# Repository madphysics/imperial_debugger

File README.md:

View this project on [CADLAB.io](https://cadlab.io/project/1894). 

# Imperial Debugger V1.1 #

USB Based multi serial port adaptor

## Overview ##

Based on an FTDI FT4232HL USB to serial chip, with 4 ports. 

The plan is to bring all points to bring them out to a standard 2x6 header

Then can use external daughter boards to do things like:

 * 1x RS232 with hardware flow control
 * 1x RS422/485 with configuration to switch between the two, wither in software or hardware.
 * 1x RS232/422 selectable
 * 1x Logic level, with external level shifter (selectable to internal 3v3)
  
## Power Supply ##

Simple switching mode from 5V USB to 3v3 on the board.
 
## Potential XCVR chips

### RS232
  * TI MAX3222E -- Looks good. Has protection in it. 250k min speeds.
    * MAX3222EEWN is WideSOIC
	  * Also available in SSOP 20 pin, which is harder to solder.
    * 4 signals, so TX/RX and CTS/RTS
	* 3222 has a shutdown pin, Active Low.

### RS422/485

  * MAX3491E
  * MAX22503
  * MAX3070-3073-3076 (3076 is fastest, all pin compatible)
  * SP330 (can do 232 as well, so could use just 3 of these?)
  
### Logic level
 
  * Ideally we want to go from 3v3 ->5V but also 3v3 > lower (2.5, 1.8)
  * LSF0204, can do 3v3 down to Ref\_A. Ref\_B Is always the higher
  * To generate 3v3 > 5V need a different route, where the signals are reversed
    Such that the input is on the Ref_B side, so could use 2 sets and jumper it.
	* Could use 3 pin jumpers, to direct the signal to one of two, or maybe use
	bus selector chip to auto do it.
  * Most ttl/cmos all work the same.

  * LSF0102 - nexperia
  * NCA9306DC - nexperia

## Potential PSU design

 * LM2594M
   * In stock, cheap.
   * ~500mA Output
   * -- **Initial choice**
 * MIC4680
   * In stock.
   * ~1A output
 * TPS5403
   * Hard to get hold of, but in stock.
 * LT1506
   * Expensive. Hard to get.
   
## Notes

 * Use externnal eeprom (SPI based) this will allow the usage of the nRI as a TXEN line for RS422/485 usage
   * 93LC56B is recommended. 16bit wide 2Kb eeprom.

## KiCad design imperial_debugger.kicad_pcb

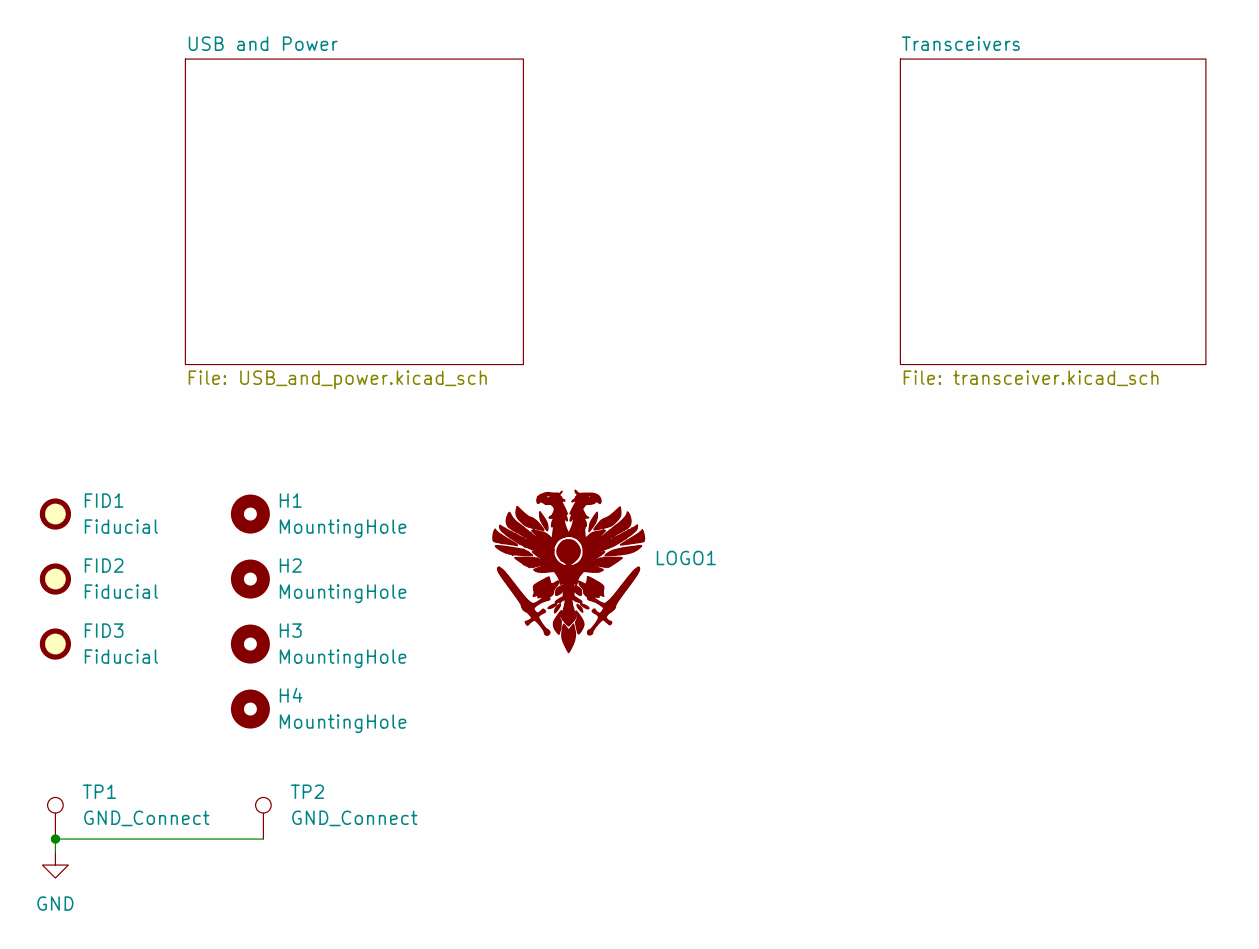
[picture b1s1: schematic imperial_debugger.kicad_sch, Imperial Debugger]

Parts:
FID1, FID2, FID3: Fiducial; Fiducial_1.5mm_Mask3mm
H1, H2, H3, H4: MountingHole; MountingHole_3.2mm_M3
LOGO1: achenar_logo
TP1, TP2: GND_Connect; TestPoint_Keystone_5000-5004_Miniature

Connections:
GND: TP1.1 (1_1), TP2.1 (1_1); also elsewhere on the board

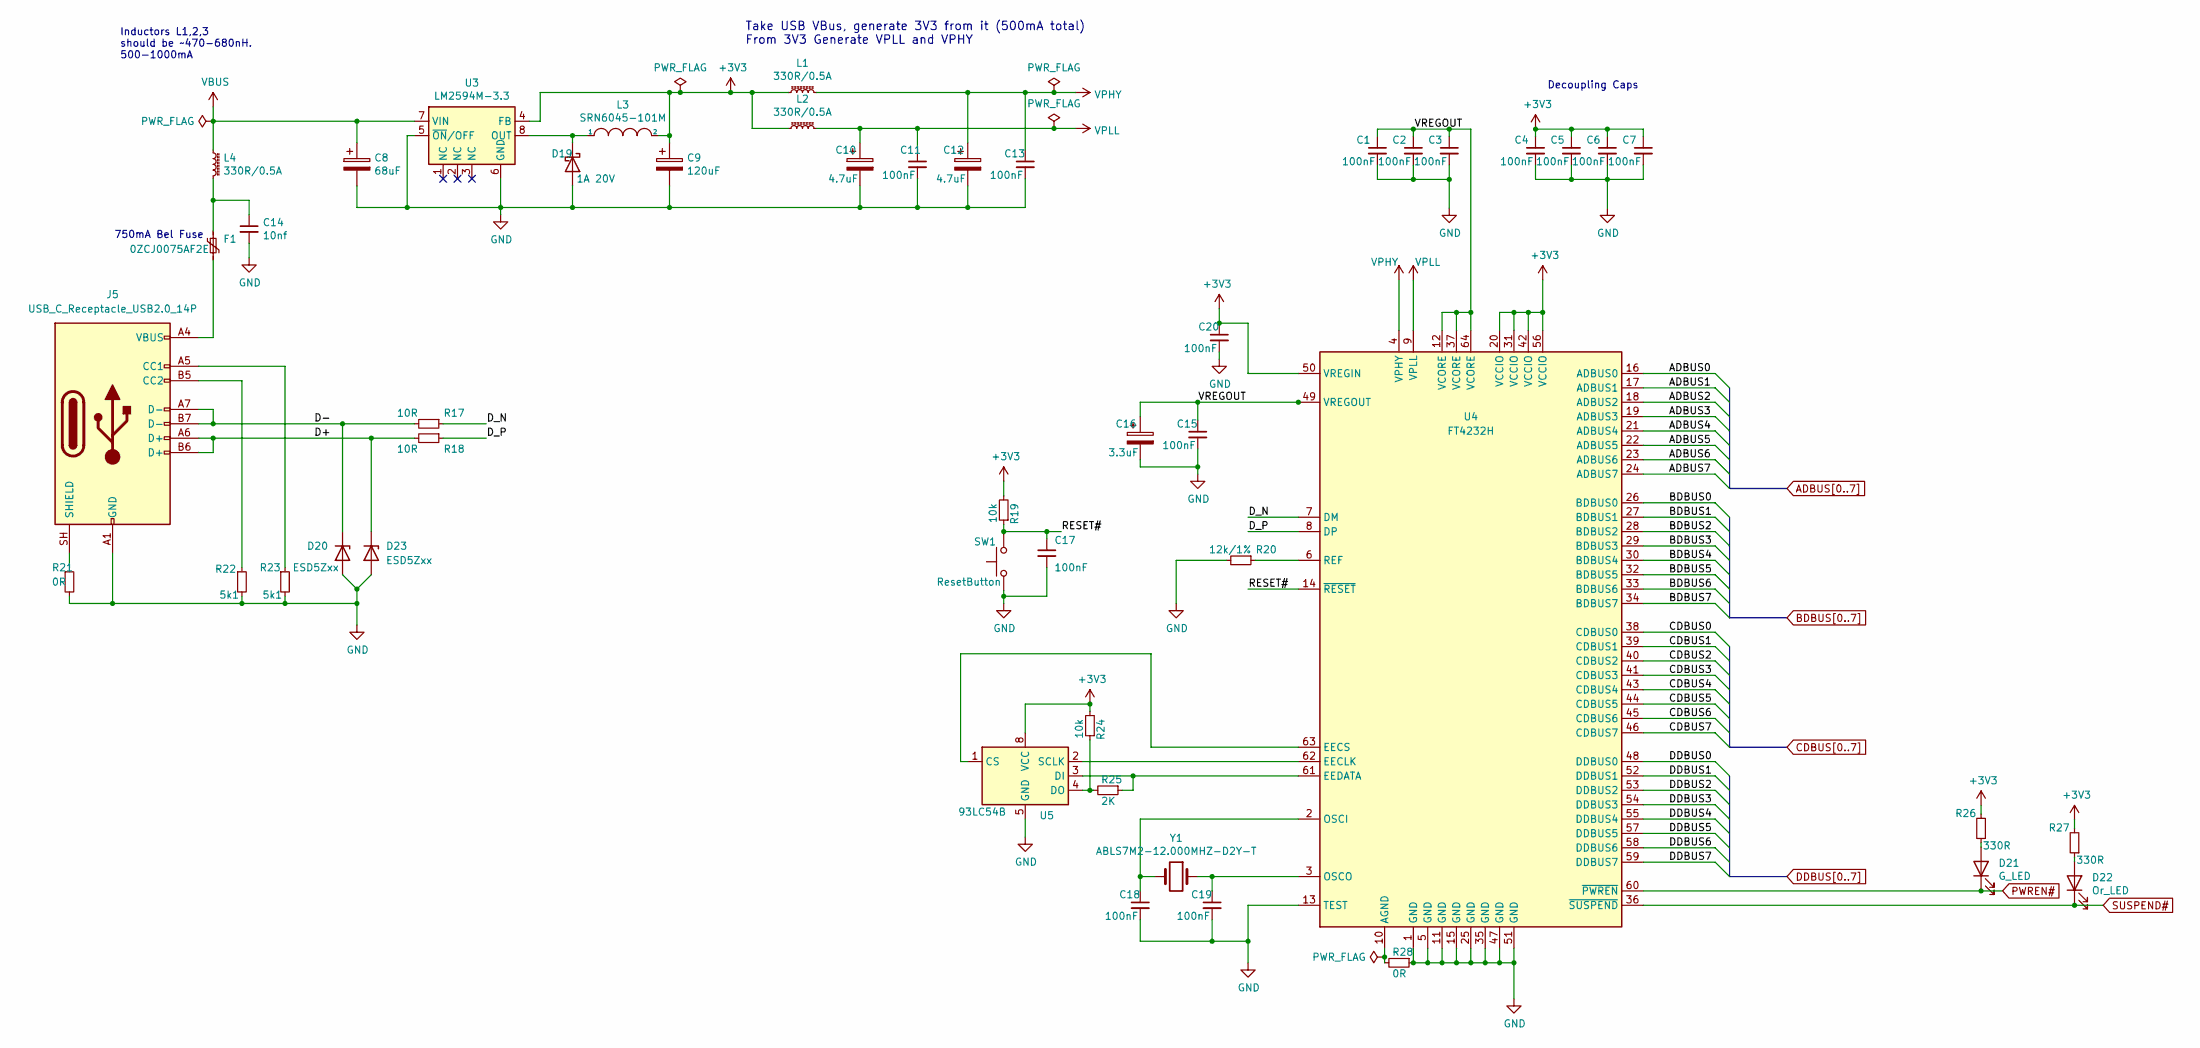
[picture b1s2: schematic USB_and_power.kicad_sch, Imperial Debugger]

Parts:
C1, C2, C3, C4, C5, C6, C7, C11, C13, C15, C17, C18, C19, C20: 100nF; C_0603_1608Metric_Pad1.08x0.95mm_HandSolder
C8: 68uF; CP_EIA-3528-21_Kemet-B_HandSolder
C9: 120uF; CP_Elec_6.3x5.7
C10, C12: 4.7uF; C_0603_1608Metric_Pad1.08x0.95mm_HandSolder
C14: 10nf; C_0603_1608Metric_Pad1.08x0.95mm_HandSolder
C16: 3.3uF; C_0603_1608Metric_Pad1.08x0.95mm_HandSolder
D19: 1A 20V; D_SOD-123
D20, D23: ESD5Zxx; D_SOD-523
D21: G_LED; LED_0603_1608Metric_Pad1.05x0.95mm_HandSolder
D22: Or_LED; LED_0603_1608Metric_Pad1.05x0.95mm_HandSolder
F1: 0ZCJ0075AF2E; R_1206_3216Metric_Pad1.30x1.75mm_HandSolder
J5: USB_C_Receptacle_USB2.0_14P; USB_C_Receptacle_HRO_TYPE-C-31-M-12
L1, L2, L4: 330R/0.5A; L_0603_1608Metric_Pad1.05x0.95mm_HandSolder
L3: SRN6045-101M; L_Bourns_SRN6045TA
R17, R18: 10R; R_0603_1608Metric_Pad0.98x0.95mm_HandSolder
R19, R24: 10k; R_0603_1608Metric_Pad0.98x0.95mm_HandSolder
R20: 12k/1%; R_0603_1608Metric_Pad0.98x0.95mm_HandSolder
R21, R28: 0R; R_0603_1608Metric_Pad0.98x0.95mm_HandSolder
R22, R23: 5k1; R_0603_1608Metric_Pad0.98x0.95mm_HandSolder
R25: 2K; R_0603_1608Metric_Pad0.98x0.95mm_HandSolder
R26, R27: 330R; R_0603_1608Metric_Pad0.98x0.95mm_HandSolder
SW1: ResetButton; SW_SPST_TS-1088-xR020
U3: LM2594M-3.3; SOIC-8_3.9x4.9mm_P1.27mm
U4: FT4232H; LQFP-64_10x10mm_P0.5mm
U5: 93LC54B; SO-8_3.9x4.9mm_P1.27mm
Y1: ABLS7M2-12.000MHZ-D2Y-T; Crystal_SMD_ECS_CSM3X-2Pin_7.6x4.1mm

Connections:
+3V3: C4.1, C5.1, C6.1, C7.1, C9.1, C20.1, L1.1, L2.1, L3.2, R19.2, R24.2, R26.2, R27.2, U3.4 (FB), U4.20 (VCCIO), U4.31 (VCCIO), U4.42 (VCCIO), U4.50 (VREGIN), U4.56 (VCCIO), U5.8 (VCC); also elsewhere on the board
/USB and Power/D+: D23.1 (K), J5.A6 (D+), J5.B6 (D+), R18.2
/USB and Power/D-: D20.1 (K), J5.A7 (D-), J5.B7 (D-), R17.2
/USB and Power/D_N: R17.1, U4.7 (DM)
/USB and Power/D_P: R18.1, U4.8 (DP)
/USB and Power/RESET#: C17.1, R19.1, SW1.2, U4.14 (~RESET)
/USB and Power/VREGOUT: C1.1, C2.1, C3.1, C15.1, C16.1, U4.12 (VCORE), U4.37 (VCORE), U4.49 (VREGOUT), U4.64 (VCORE)
ADBUS0: U4.16 (ADBUS0); also elsewhere on the board
ADBUS1: U4.17 (ADBUS1); also elsewhere on the board
ADBUS2: U4.18 (ADBUS2); also elsewhere on the board
ADBUS3: U4.19 (ADBUS3); also elsewhere on the board
ADBUS4: U4.21 (ADBUS4); also elsewhere on the board
ADBUS5: U4.22 (ADBUS5)
ADBUS6: U4.23 (ADBUS6)
ADBUS7: U4.24 (ADBUS7); also elsewhere on the board
BDBUS0: U4.26 (BDBUS0); also elsewhere on the board
BDBUS1: U4.27 (BDBUS1); also elsewhere on the board
BDBUS2: U4.28 (BDBUS2); also elsewhere on the board
BDBUS3: U4.29 (BDBUS3); also elsewhere on the board
BDBUS4: U4.30 (BDBUS4); also elsewhere on the board
BDBUS5: U4.32 (BDBUS5)
BDBUS6: U4.33 (BDBUS6)
BDBUS7: U4.34 (BDBUS7); also elsewhere on the board
CDBUS0: U4.38 (CDBUS0); also elsewhere on the board
CDBUS1: U4.39 (CDBUS1); also elsewhere on the board
CDBUS2: U4.40 (CDBUS2); also elsewhere on the board
CDBUS3: U4.41 (CDBUS3); also elsewhere on the board
CDBUS4: U4.43 (CDBUS4); also elsewhere on the board
CDBUS5: U4.44 (CDBUS5)
CDBUS6: U4.45 (CDBUS6)
CDBUS7: U4.46 (CDBUS7); also elsewhere on the board
DDBUS0: U4.48 (DDBUS0); also elsewhere on the board
DDBUS1: U4.52 (DDBUS1); also elsewhere on the board
DDBUS2: U4.53 (DDBUS2); also elsewhere on the board
DDBUS3: U4.54 (DDBUS3); also elsewhere on the board
DDBUS4: U4.55 (DDBUS4); also elsewhere on the board
DDBUS5: U4.57 (DDBUS5)
DDBUS6: U4.58 (DDBUS6)
DDBUS7: U4.59 (DDBUS7); also elsewhere on the board
GND: C1.2, C2.2, C3.2, C4.2, C5.2, C6.2, C7.2, C8.2, C9.2, C10.2, C11.2, C12.2, C13.2, C14.2, C15.2, C16.2, C17.2, C18.2, C19.2, C20.2, D19.2 (A), D20.2 (A), D23.2 (A), J5.A1 (GND), J5.A12 (GND), J5.B1 (GND), J5.B12 (GND), R20.2, R21.2, R22.2, R23.2, R28.1, SW1.1, U3.5 (~ON/OFF), U3.6 (GND), U4.1 (GND), U4.5 (GND), U4.11 (GND), U4.13 (TEST), U4.15 (GND), U4.25 (GND), U4.35 (GND), U4.47 (GND), U4.51 (GND), U5.5 (GND); also elsewhere on the board
unnamed: C14.1, F1.1, L4.2
unnamed: D19.1 (K), L3.1, U3.8 (OUT)
unnamed: D21.2 (A), R26.1
unnamed: D22.2 (A), R27.1
unnamed: F1.2, J5.A4 (VBUS), J5.A9 (VBUS), J5.B4 (VBUS), J5.B9 (VBUS)
unnamed: J5.A5 (CC1), R23.1
unnamed: J5.B5 (CC2), R22.1
unnamed: J5.SH (SHIELD), R21.1
unnamed: R28.2, U4.10 (AGND)
unnamed: U4.62 (EECLK), U5.2 (SCLK)
unnamed: U4.63 (EECS), U5.1 (CS)
unnamed: R25.1, U4.61 (EEDATA), U5.3 (DI)
unnamed: C18.1, U4.2 (OSCI), Y1.2
unnamed: C19.1, U4.3 (OSCO), Y1.1
unnamed: R20.1, U4.6 (REF)
unnamed: R24.1, R25.2, U5.4 (DO)
PWREN#: D21.1 (K), U4.60 (~PWREN); also elsewhere on the board
SUSPEND#: D22.1 (K), U4.36 (~SUSPEND); also elsewhere on the board
VBUS: C8.1, L4.1, U3.7 (VIN); also elsewhere on the board
VPHY: C12.1, C13.1, L1.2, U4.4 (VPHY)
VPLL: C10.1, C11.1, L2.2, U4.9 (VPLL)

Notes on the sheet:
Decoupling Caps
Take USB VBus, generate 3V3 from it (500mA total) From 3V3 Generate VPLL and VPHY
750mA Bel Fuse
Inductors L1,2,3 should be ~470-680nH. 500-1000mA

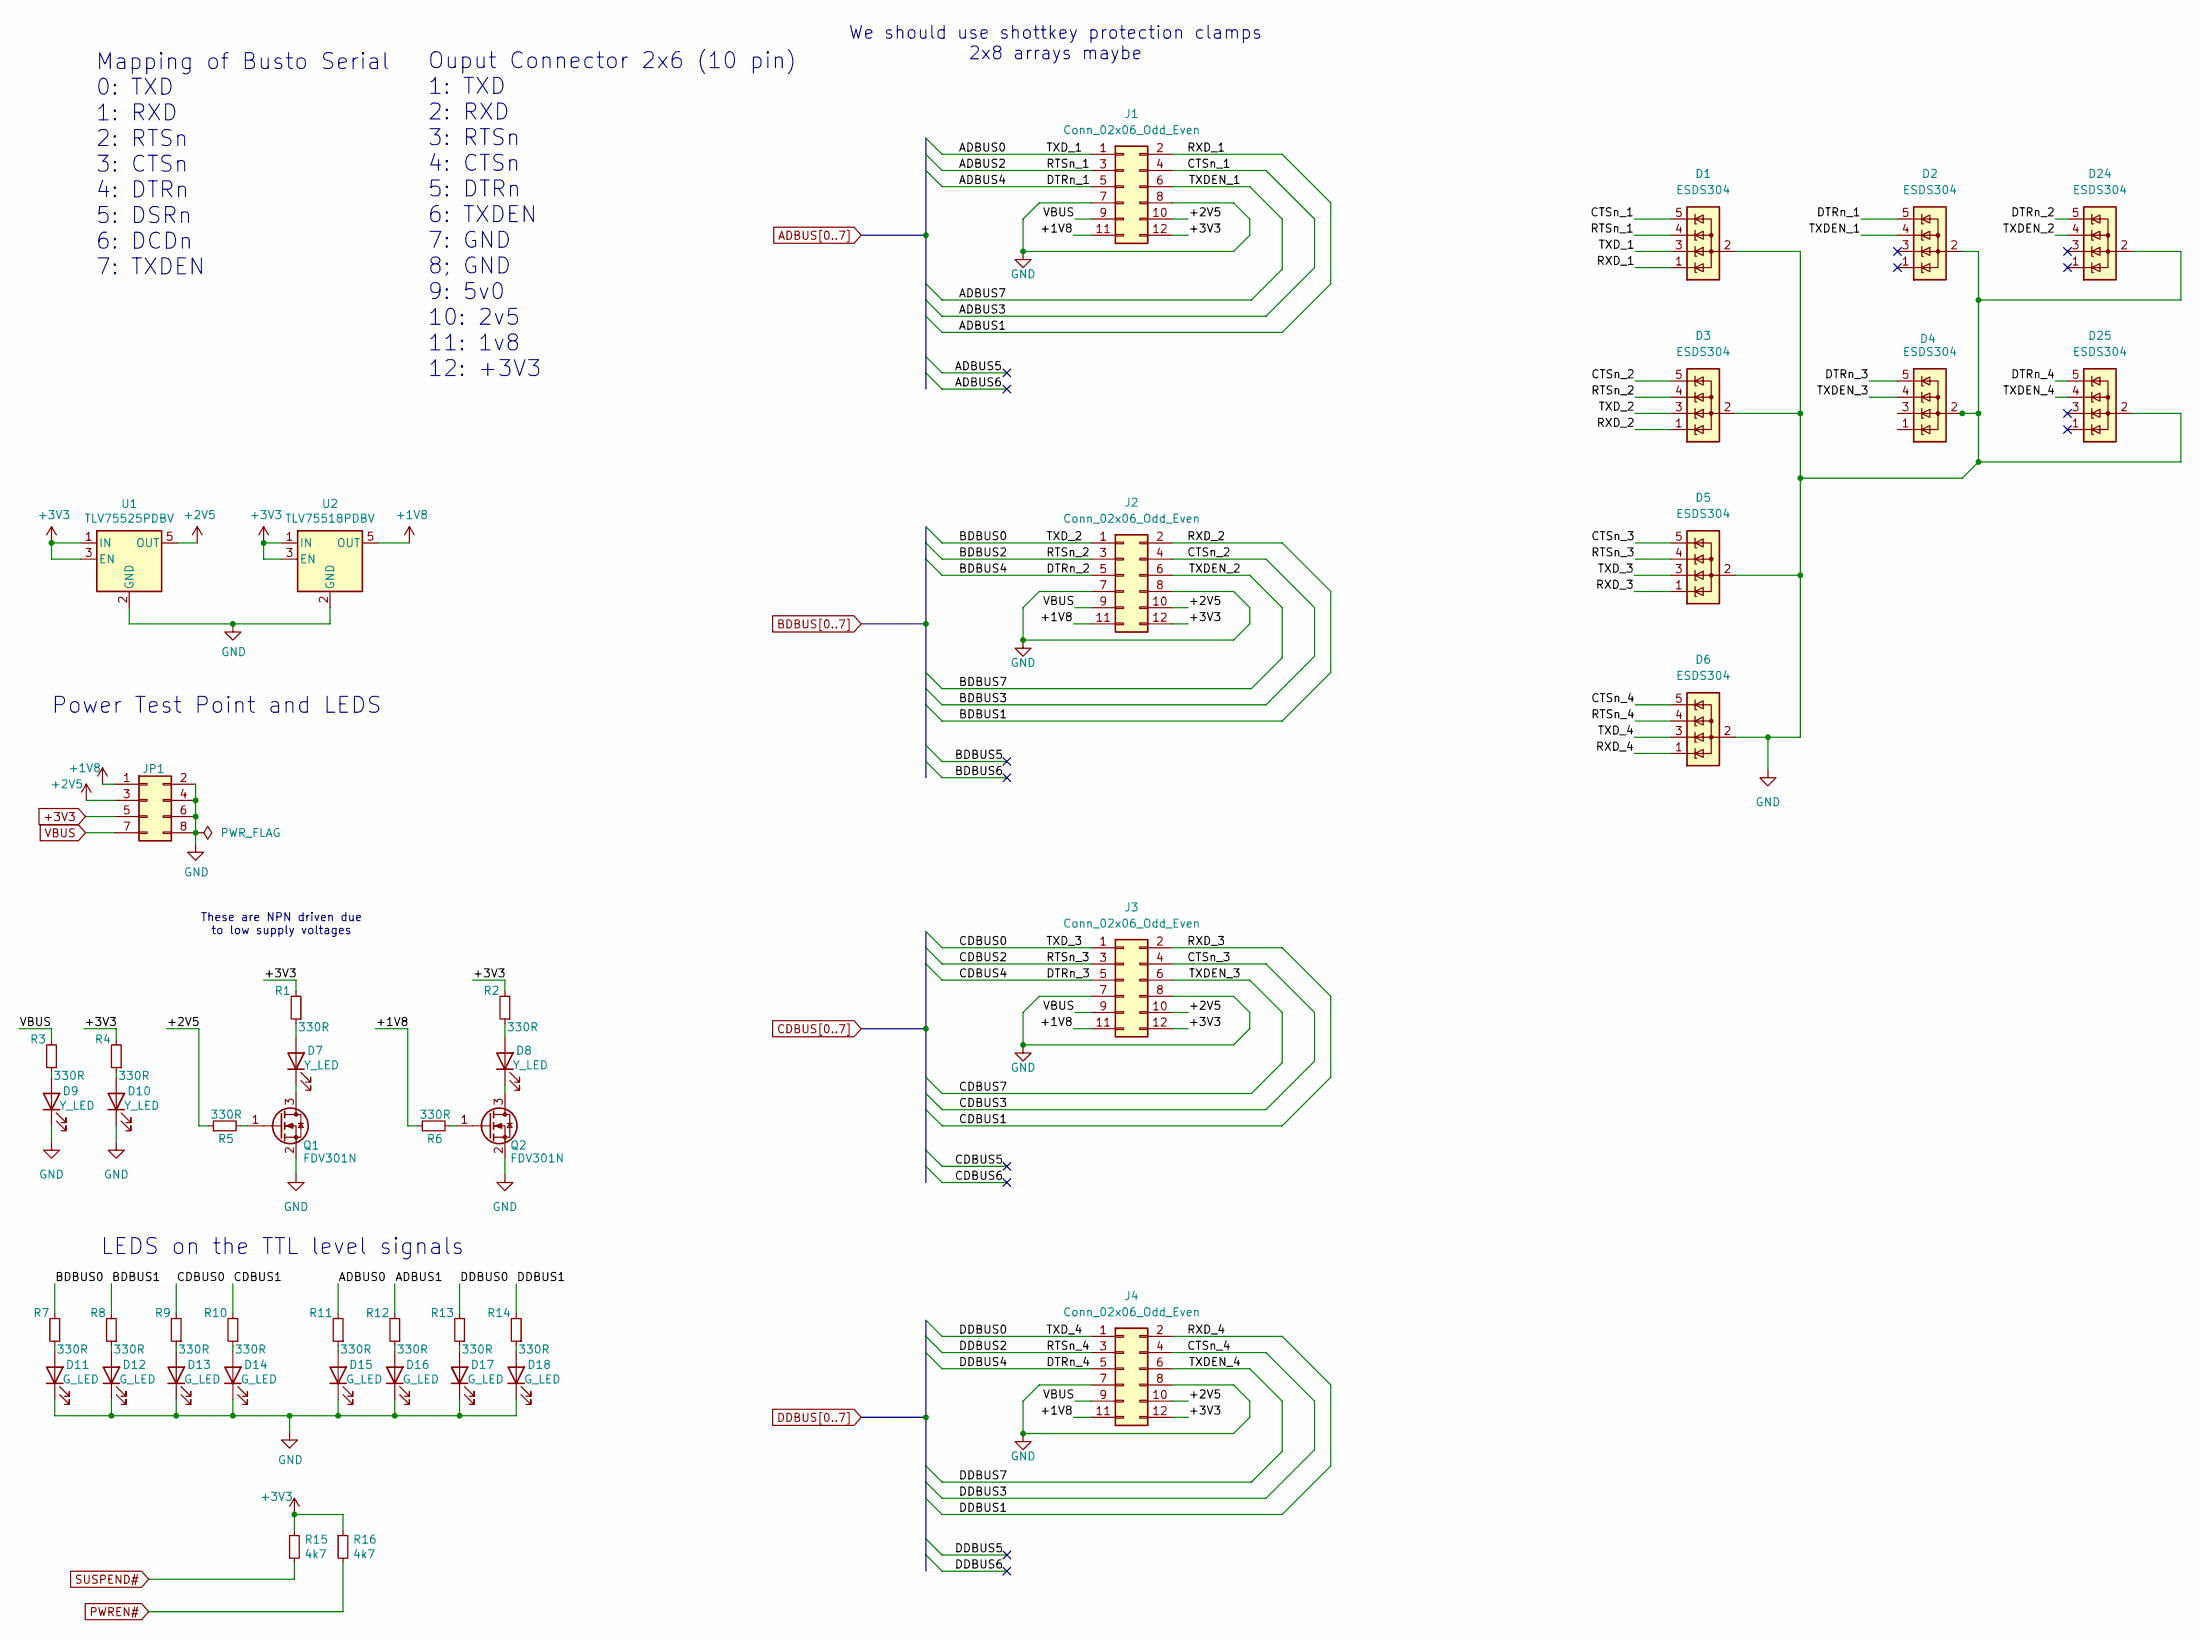
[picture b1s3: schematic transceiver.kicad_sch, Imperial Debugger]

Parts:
D1, D2, D3, D4, D5, D6, D24, D25: ESDS304; SOT-23-5
D7, D8, D9, D10: Y_LED; LED_0603_1608Metric_Pad1.05x0.95mm_HandSolder
D11, D12, D13, D14, D15, D16, D17, D18: G_LED; LED_0603_1608Metric_Pad1.05x0.95mm_HandSolder
J1, J2, J3, J4: Conn_02x06_Odd_Even; PinSocket_2x06_P2.54mm_Horizontal
JP1: Jumper; PinHeader_2x04_P1.27mm_Vertical_SMD
Q1, Q2: FDV301N; SOT-23
R1, R2, R3, R4, R5, R6, R7, R8, R9, R10, R11, R12, R13, R14: 330R; R_0603_1608Metric_Pad0.98x0.95mm_HandSolder
R15, R16: 4k7; R_0603_1608Metric_Pad0.98x0.95mm_HandSolder
U1: TLV75525PDBV; SOT-23-5
U2: TLV75518PDBV; SOT-23-5

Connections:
+1V8: J1.11, J2.11, J3.11, J4.11, JP1.1, R6.1, U2.5 (OUT)
+2V5: J1.10, J2.10, J3.10, J4.10, JP1.3, R5.1, U1.5 (OUT)
+3V3: J1.12, J2.12, J3.12, J4.12, JP1.5, R1.2, R2.2, R4.2, R15.1, R16.1, U1.1 (IN), U1.3 (EN), U2.1 (IN), U2.3 (EN); also elsewhere on the board
ADBUS0: D1.3 (K), J1.1, R11.2; also elsewhere on the board
ADBUS1: D1.1 (K), J1.2, R12.2; also elsewhere on the board
ADBUS2: D1.4 (K), J1.3; also elsewhere on the board
ADBUS3: D1.5 (K), J1.4; also elsewhere on the board
ADBUS4: D2.5 (K), J1.5; also elsewhere on the board
ADBUS7: D2.4 (K), J1.6; also elsewhere on the board
BDBUS0: D3.3 (K), J2.1, R7.2; also elsewhere on the board
BDBUS1: D3.1 (K), J2.2, R8.2; also elsewhere on the board
BDBUS2: D3.4 (K), J2.3; also elsewhere on the board
BDBUS3: D3.5 (K), J2.4; also elsewhere on the board
BDBUS4: D24.5 (K), J2.5; also elsewhere on the board
BDBUS7: D24.4 (K), J2.6; also elsewhere on the board
CDBUS0: D5.3 (K), J3.1, R9.2; also elsewhere on the board
CDBUS1: D5.1 (K), J3.2, R10.2; also elsewhere on the board
CDBUS2: D5.4 (K), J3.3; also elsewhere on the board
CDBUS3: D5.5 (K), J3.4; also elsewhere on the board
CDBUS4: D4.5 (K), J3.5; also elsewhere on the board
CDBUS7: D4.4 (K), J3.6; also elsewhere on the board
DDBUS0: D6.3 (K), J4.1, R13.2; also elsewhere on the board
DDBUS1: D6.1 (K), J4.2, R14.2; also elsewhere on the board
DDBUS2: D6.4 (K), J4.3; also elsewhere on the board
DDBUS3: D6.5 (K), J4.4; also elsewhere on the board
DDBUS4: D25.5 (K), J4.5; also elsewhere on the board
DDBUS7: D25.4 (K), J4.6; also elsewhere on the board
GND: D1.2 (A), D2.2 (A), D3.2 (A), D4.2 (A), D5.2 (A), D6.2 (A), D9.1 (K), D10.1 (K), D11.1 (K), D12.1 (K), D13.1 (K), D14.1 (K), D15.1 (K), D16.1 (K), D17.1 (K), D18.1 (K), D24.2 (A), D25.2 (A), J1.7, J1.8, J2.7, J2.8, J3.7, J3.8, J4.7, J4.8, JP1.2, JP1.4, JP1.6, JP1.8, Q1.2 (S), Q2.2 (S), U1.2 (GND), U2.2 (GND); also elsewhere on the board
unnamed: D7.2 (A), R1.1
unnamed: D7.1 (K), Q1.3 (D)
unnamed: D8.2 (A), R2.1
unnamed: D8.1 (K), Q2.3 (D)
unnamed: D9.2 (A), R3.1
unnamed: D10.2 (A), R4.1
unnamed: D11.2 (A), R7.1
unnamed: D12.2 (A), R8.1
unnamed: D13.2 (A), R9.1
unnamed: D14.2 (A), R10.1
unnamed: D15.2 (A), R11.1
unnamed: D16.2 (A), R12.1
unnamed: D17.2 (A), R13.1
unnamed: D18.2 (A), R14.1
unnamed: Q1.1 (G), R5.2
unnamed: Q2.1 (G), R6.2
PWREN#: R16.2; also elsewhere on the board
SUSPEND#: R15.2; also elsewhere on the board
VBUS: J1.9, J2.9, J3.9, J4.9, JP1.7, R3.2; also elsewhere on the board

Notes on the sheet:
LEDS on the TTL level signals
Ouput Connector 2x6 (10 pin) 1: TXD 2: RXD 3: RTSn 4: CTSn 5: DTRn 6: TXDEN 7: GND 8; GND 9: 5v0 10: 2v5 11: 1v8 12: +3V3
Power Test Point and LEDS
These are NPN driven due to low supply voltages
We should use shottkey protection clamps 2x8 arrays maybe
Mapping of Busto Serial 0: TXD 1: RXD 2: RTSn 3: CTSn 4: DTRn 5: DSRn 6: DCDn 7: TXDEN

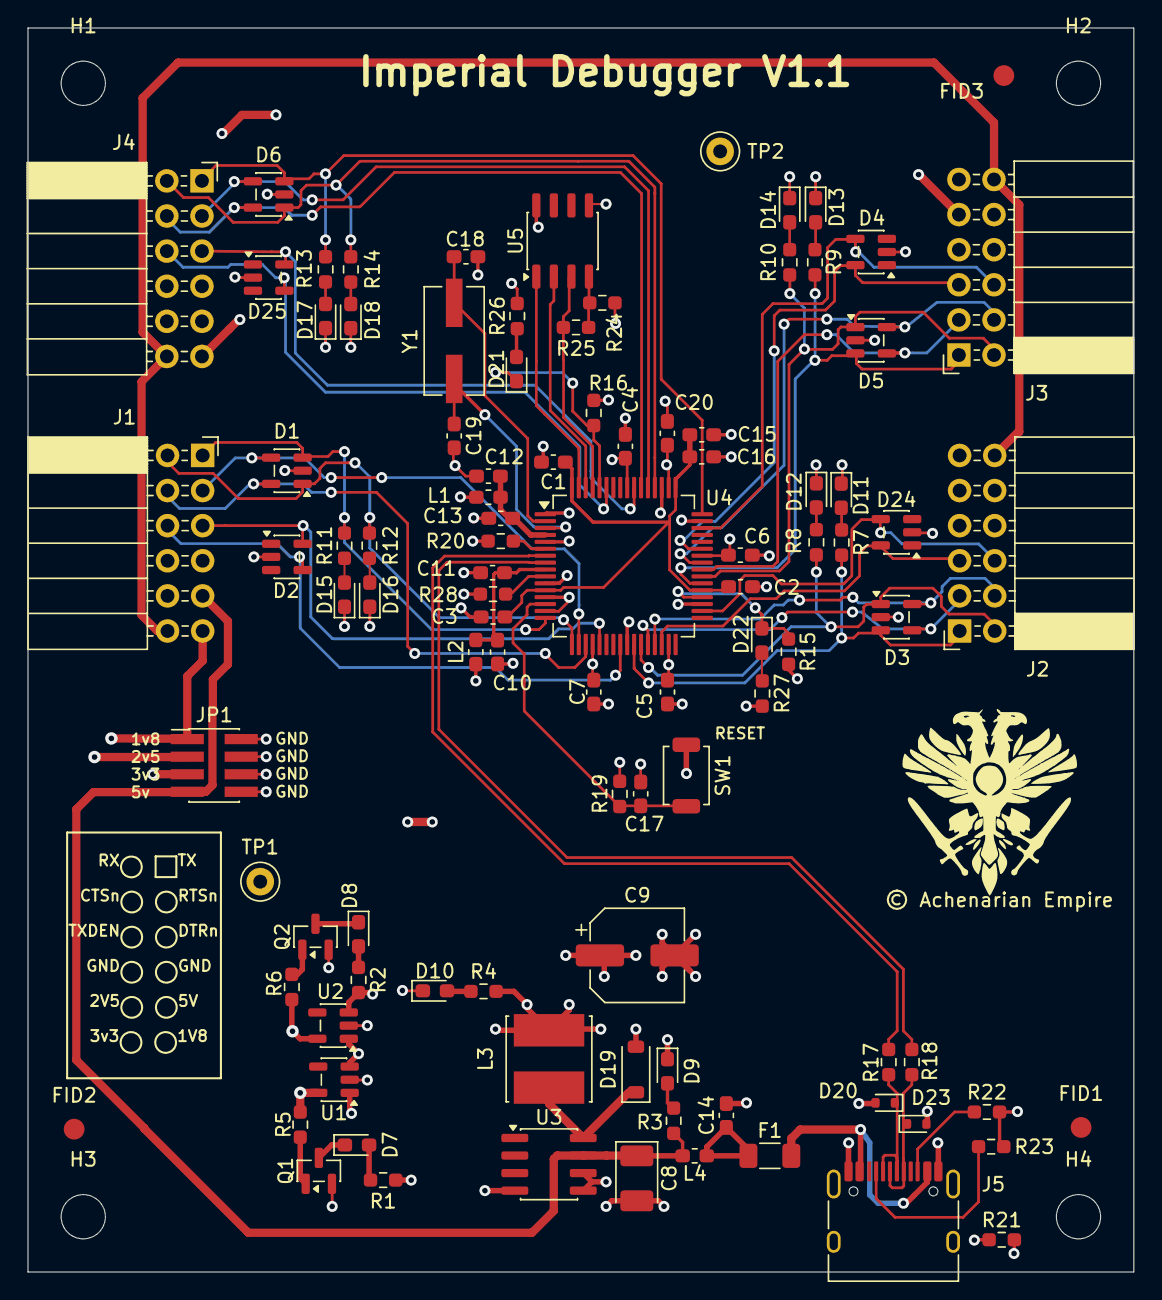
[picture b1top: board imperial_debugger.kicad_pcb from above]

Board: 4 copper layers, 80.0 x 90.0 mm, 103 parts (0 on the bottom side), 71 nets.

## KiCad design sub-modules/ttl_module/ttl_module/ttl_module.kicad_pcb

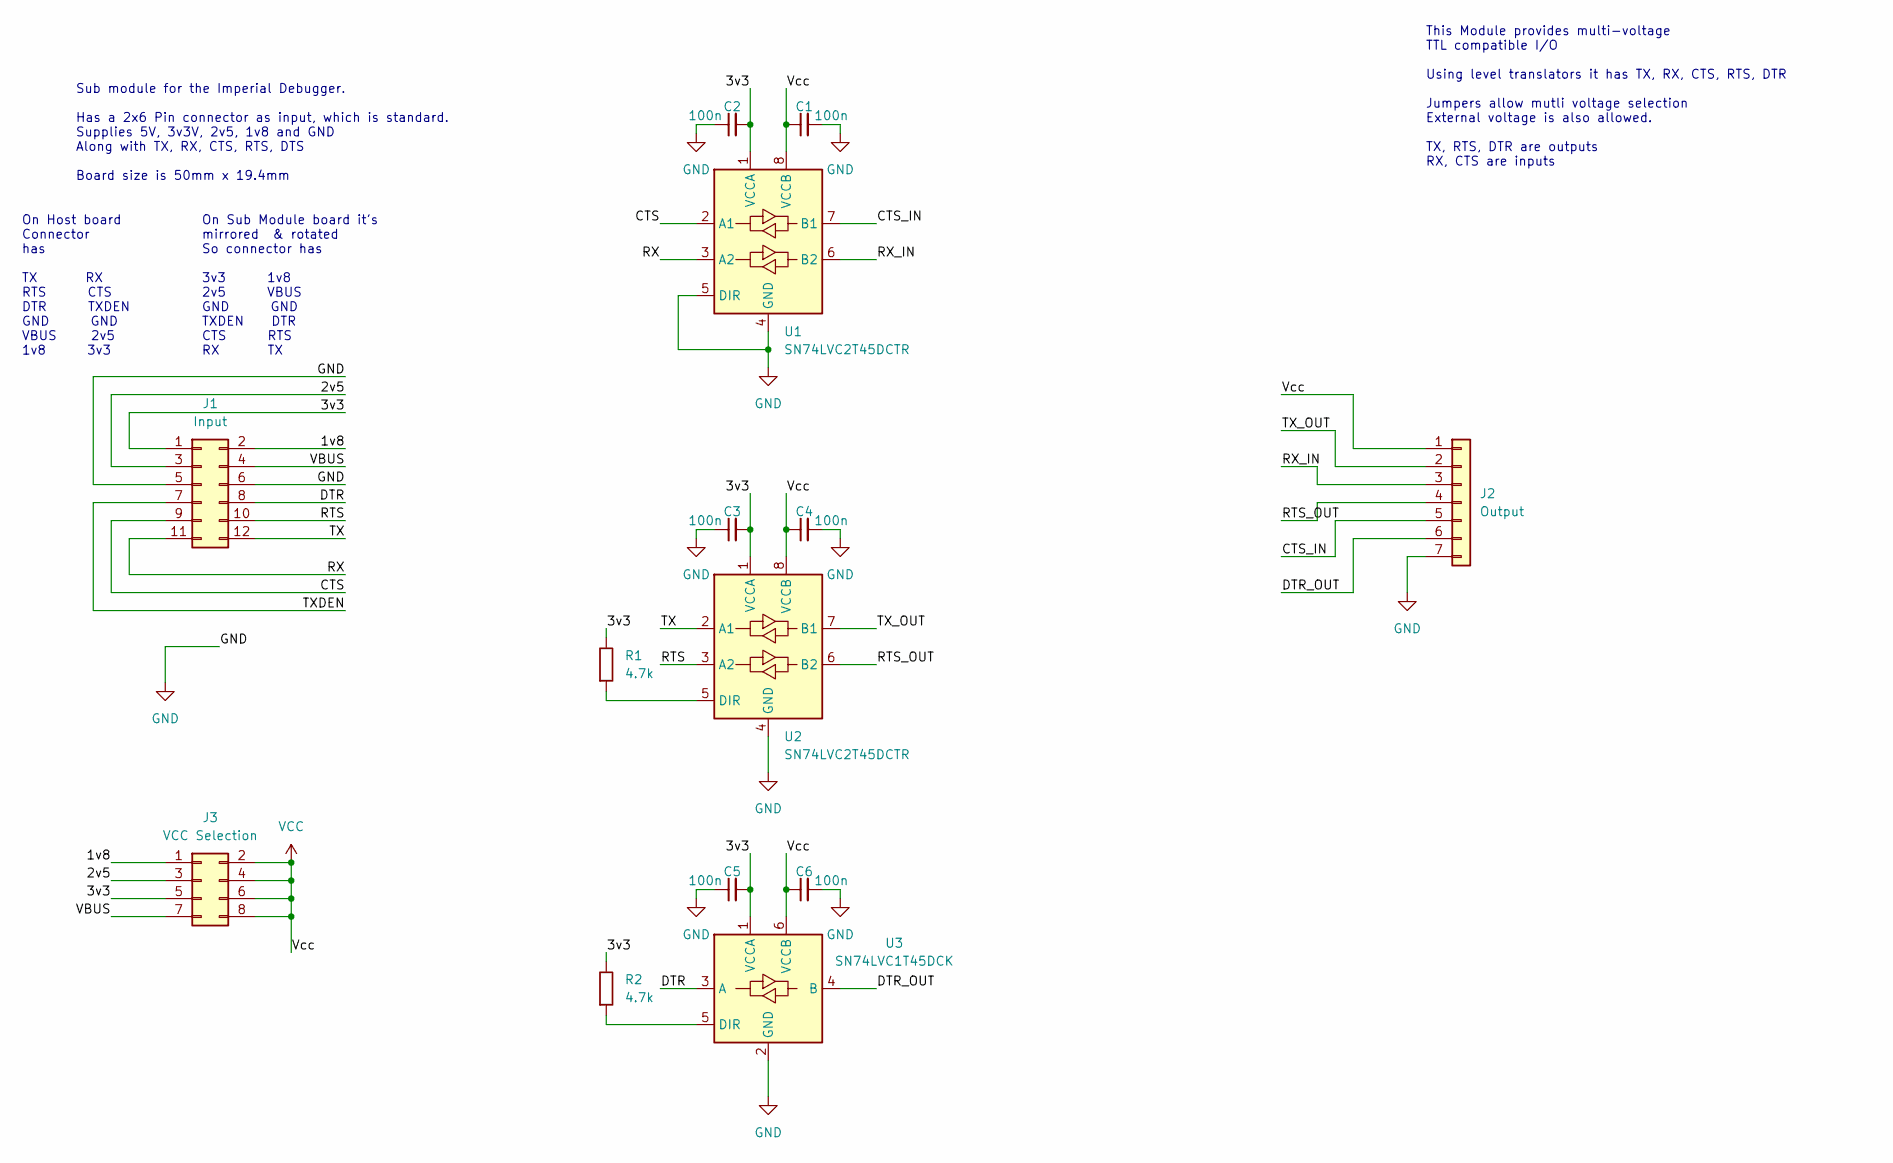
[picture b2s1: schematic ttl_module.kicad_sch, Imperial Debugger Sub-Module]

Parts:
C1, C2, C3, C4, C5, C6: 100n; C_0603_1608Metric_Pad1.08x0.95mm_HandSolder
J1: Input; PinSocket_2x06_P2.54mm_Horizontal
J2: Output; PinHeader_1x07_P2.54mm_Vertical
J3: VCC Selection; PinHeader_2x04_P2.54mm_Vertical
R1, R2: 4.7k; R_0603_1608Metric_Pad0.98x0.95mm_HandSolder
U1, U2: SN74LVC2T45DCTR; SOP65P400X130-8N
U3: SN74LVC1T45DCK; SOT-363_SC-70-6

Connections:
/1v8: J1.2, J3.1
/2v5: J1.3, J3.3
/3v3: C2.2, C3.2, C5.2, J1.1, J3.5, R1.2, R2.2, U1.1 (VCCA), U2.1 (VCCA), U3.1 (VCCA)
/CTS: J1.9, U1.2 (A1)
/CTS_IN: J2.5, U1.7 (B1)
/DTR: J1.8, U3.3 (A)
/DTR_OUT: J2.6, U3.4 (B)
/RTS: J1.10, U2.3 (A2)
/RTS_OUT: J2.4, U2.6 (B2)
/RX: J1.11, U1.3 (A2)
/RX_IN: J2.3, U1.6 (B2)
/TX: J1.12, U2.2 (A1)
/TXDEN: J1.7
/TX_OUT: J2.2, U2.7 (B1)
/VBUS: J1.4, J3.7
GND: C1.2, C2.1, C3.1, C4.2, C5.1, C6.2, J1.5, J1.6, J2.7, U1.4 (GND), U1.5 (DIR), U2.4 (GND), U3.2 (GND)
unnamed: R1.1, U2.5 (DIR)
unnamed: R2.1, U3.5 (DIR)
VCC: C1.1, C4.1, C6.1, J2.1, J3.2, J3.4, J3.6, J3.8, U1.8 (VCCB), U2.8 (VCCB), U3.6 (VCCB)

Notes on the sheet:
Sub module for the Imperial Debugger. Has a 2x6 Pin connector as input, which is standard. Supplies 5V, 3v3V, 2v5, 1v8 and GND Along with TX, RX, CTS, RTS, DTS Board size is 50mm x 19.4mm
On Host board Connector has TX RX RTS CTS DTR TXDEN GND GND VBUS 2v5 1v8 3v3
This Module provides multi-voltage TTL compatible I/O Using level translators it has TX, RX, CTS, RTS, DTR Jumpers allow mutli voltage selection External voltage is also allowed. TX, RTS, DTR are outputs RX, CTS are inputs
On Sub Module board it's mirrored & rotated So connector has 3v3 1v8 2v5 VBUS GND GND TXDEN DTR CTS RTS RX TX

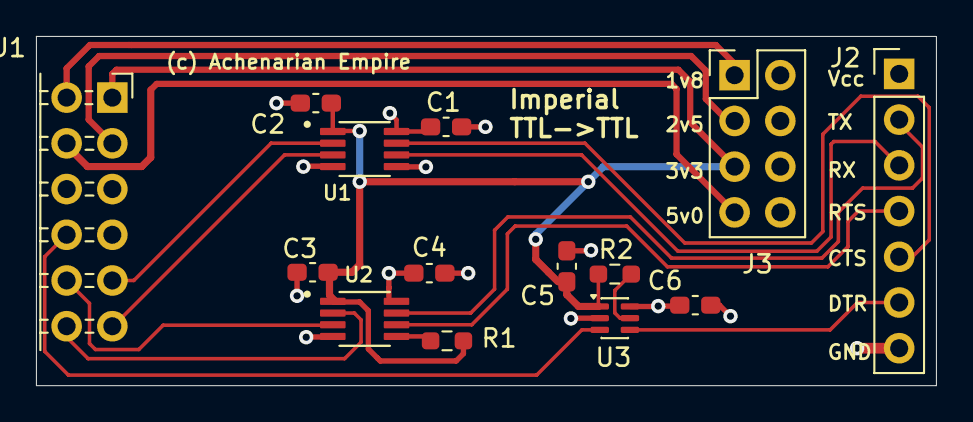
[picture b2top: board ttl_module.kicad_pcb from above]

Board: 2 copper layers, 50.0 x 19.4 mm, 14 parts (0 on the bottom side), 18 nets.

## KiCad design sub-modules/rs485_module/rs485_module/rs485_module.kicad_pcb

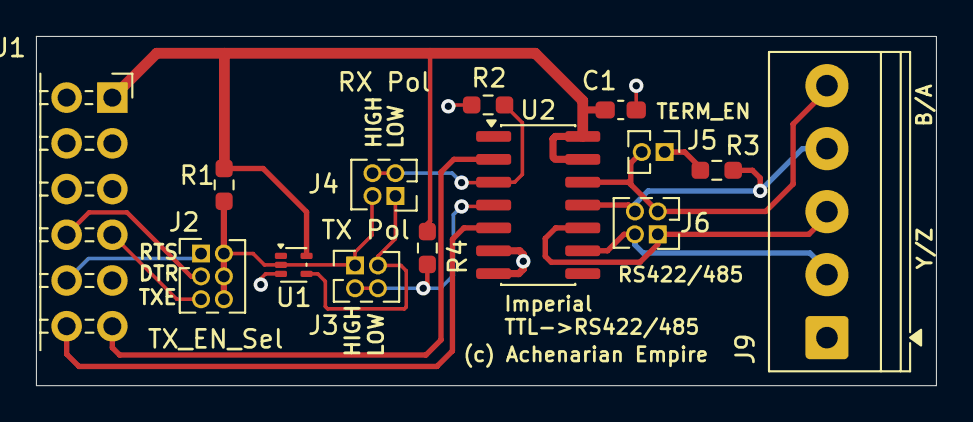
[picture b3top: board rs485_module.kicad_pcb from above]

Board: 2 copper layers, 50.0 x 19.4 mm, 14 parts (0 on the bottom side), 16 nets.

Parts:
C1: 100n; C_0603_1608Metric_Pad1.08x0.95mm_HandSolder
J1: Conn_02x06_Odd_Even; PinSocket_2x06_P2.54mm_Horizontal
J2: TX_EN_Sel; PinHeader_2x03_P1.27mm_Vertical
J3: TX Pol; PinHeader_2x02_P1.27mm_Vertical
J4: RX Pol; PinHeader_2x02_P1.27mm_Vertical
J5: TERM_EN; PinHeader_1x02_P1.27mm_Vertical
J6: RS422/485; PinHeader_2x02_P1.27mm_Vertical
J9: MKDS 1/ 5-3,5; TerminalBlock_Phoenix_PT-1,5-5-3.5-H_1x05_P3.50mm_Horizontal
R1, R2, R4: 10k; R_0603_1608Metric_Pad0.98x0.95mm_HandSolder
R3: 120R; R_0603_1608Metric_Pad0.98x0.95mm_HandSolder
U1: 74LVC1GU04DRL; SOT-553
U2: ADM3491ExR; SOIC-14_3.9x8.7mm_P1.27mm

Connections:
+3V3: C1.2, J1.1, R1.1, R4.1, U1.5 (VCC), U2.13 (VCC), U2.14 (VCC)
/A: J5.2, J6.3, J9.5, U2.12 (A)
/B: J6.4, J9.4, R3.2, U2.11 (B)
/DE: J3.3, J3.4, R4.2, U2.4 (DE)
/DTR: J1.8, J2.3
/RTS: J1.10, J2.1
/RX: J1.11, U2.2 (RO)
/TX: J1.12, U2.5 (DI)
/TXDEN: J1.7, J2.5
/TX_EN: J2.2, J2.4, J2.6, J3.1, J4.2, R1.2, U1.2
/Y: J6.2, J9.2, U2.9 (Y)
/Z: J6.1, J9.3, U2.10 (Z)
/~RE: J4.3, J4.4, R2.1, U2.3 (~RE)
/~TX_EN: J3.2, J4.1, U1.4
GND: C1.1, J1.5, J1.6, J9.1, R2.2, U1.3 (GND), U2.6 (GND), U2.7 (GND)
unnamed: J5.1, R3.1

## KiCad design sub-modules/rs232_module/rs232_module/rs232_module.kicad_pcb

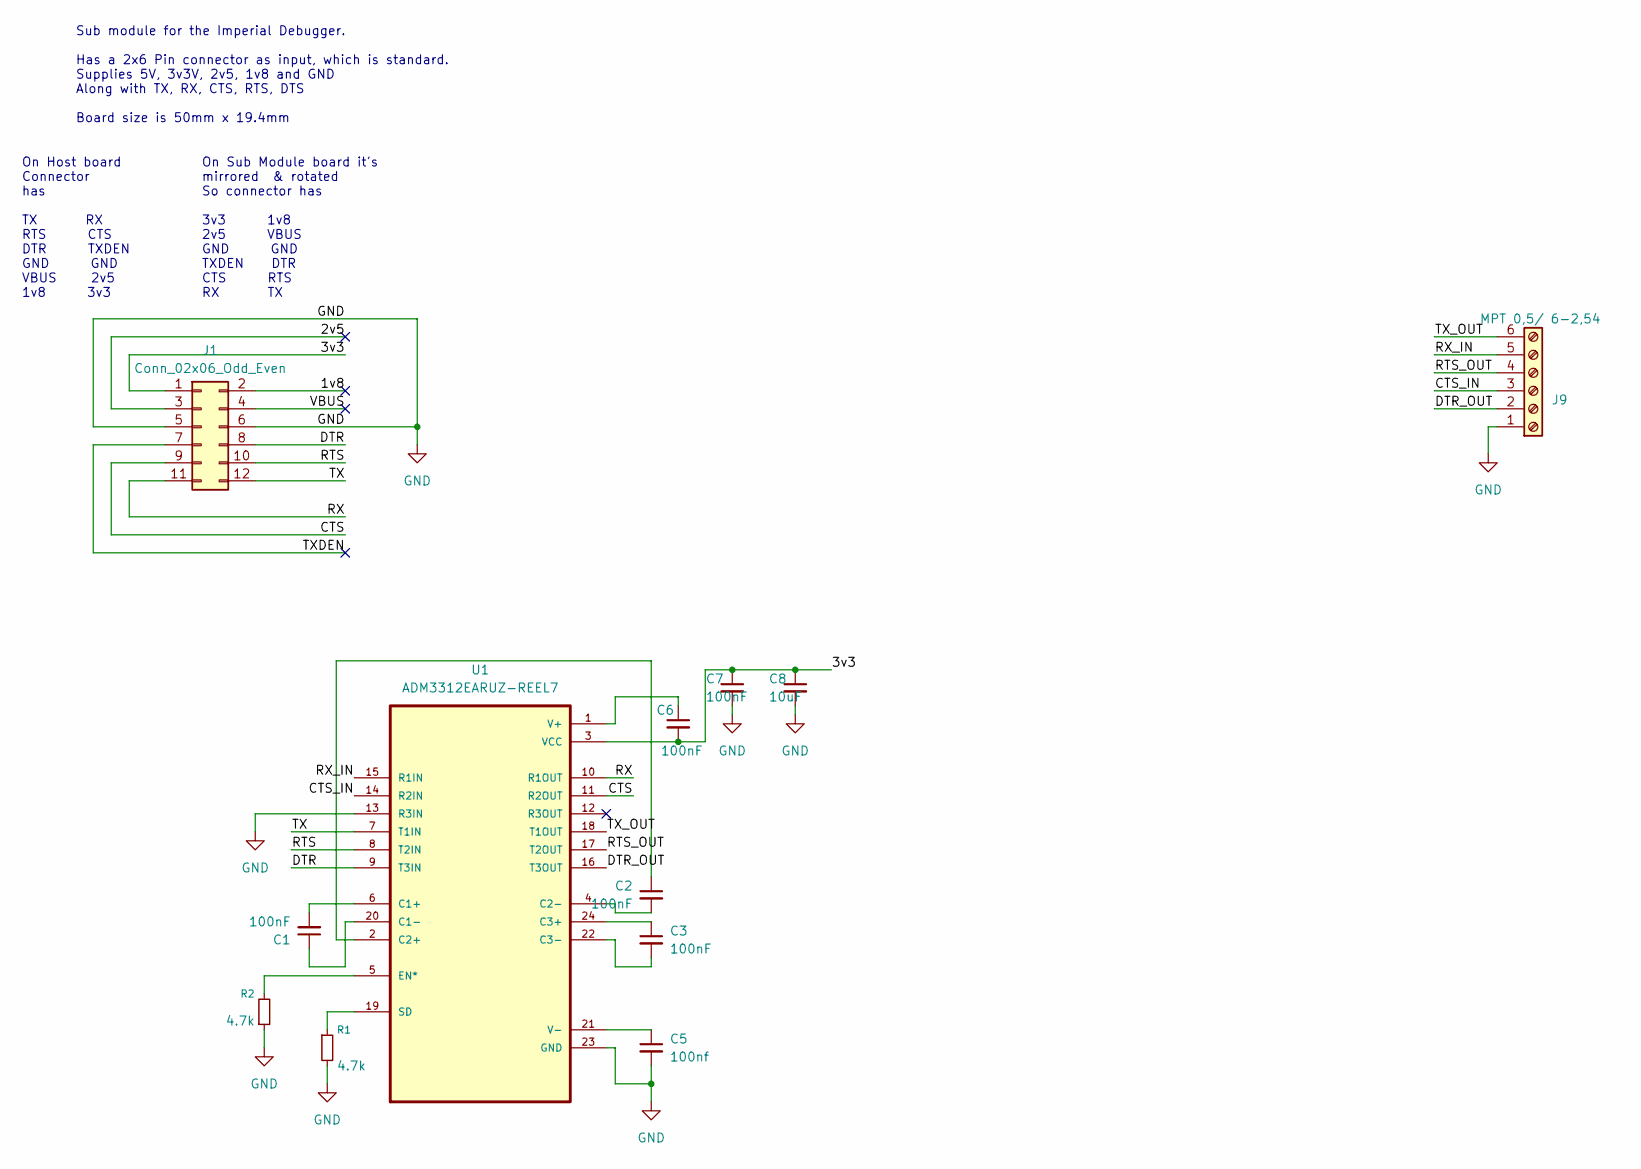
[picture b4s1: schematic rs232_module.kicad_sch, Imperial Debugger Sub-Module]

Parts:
C1, C2, C3, C6, C7: 100nF; C_0603_1608Metric_Pad1.08x0.95mm_HandSolder
C5: 100nf; C_0603_1608Metric_Pad1.08x0.95mm_HandSolder
C8: 10uF; CP_EIA-3528-12_Kemet-T_HandSolder
J1: Conn_02x06_Odd_Even; PinSocket_2x06_P2.54mm_Horizontal
J9: MPT 0,5/ 6-2,54; TerminalBlock_Phoenix_MPT-0,5-6-2.54_1x06_P2.54mm_Horizontal
R1, R2: 4.7k; R_0603_1608Metric_Pad0.98x0.95mm_HandSolder
U1: ADM3312EARUZ-REEL7; SOP65P640X120-24N; DigiKey_Part_Number 505-ADM3312EARUZ-REEL7CT-ND

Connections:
/1v8: J1.2
/2v5: J1.3
/3v3: C6.2, C7.1, C8.1, J1.1, U1.3 (VCC)
/CTS: J1.9, U1.11 (R2OUT)
/CTS_IN: J9.3, U1.14 (R2IN)
/DTR: J1.8, U1.9 (T3IN)
/DTR_OUT: J9.2, U1.16 (T3OUT)
/RTS: J1.10, U1.8 (T2IN)
/RTS_OUT: J9.4, U1.17 (T2OUT)
/RX: J1.11, U1.10 (R1OUT)
/RX_IN: J9.5, U1.15 (R1IN)
/TX: J1.12, U1.7 (T1IN)
/TXDEN: J1.7
/TX_OUT: J9.6, U1.18 (T1OUT)
/VBUS: J1.4
GND: C5.2, C7.2, C8.2, J1.5, J1.6, J9.1, R1.2, R2.1, U1.13 (R3IN), U1.23 (GND)
unnamed: C1.2, U1.6 (C1+)
unnamed: C1.1, U1.20 (C1-)
unnamed: C2.1, U1.2 (C2+)
unnamed: C2.2, U1.4 (C2-)
unnamed: C3.1, U1.24 (C3+)
unnamed: C3.2, U1.22 (C3-)
unnamed: R2.2, U1.5 (EN*)
unnamed: R1.1, U1.19 (SD)
unnamed: C6.1, U1.1 (V+)
unnamed: C5.1, U1.21 (V-)

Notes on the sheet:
Sub module for the Imperial Debugger. Has a 2x6 Pin connector as input, which is standard. Supplies 5V, 3v3V, 2v5, 1v8 and GND Along with TX, RX, CTS, RTS, DTS Board size is 50mm x 19.4mm
On Host board Connector has TX RX RTS CTS DTR TXDEN GND GND VBUS 2v5 1v8 3v3
On Sub Module board it's mirrored & rotated So connector has 3v3 1v8 2v5 VBUS GND GND TXDEN DTR CTS RTS RX TX

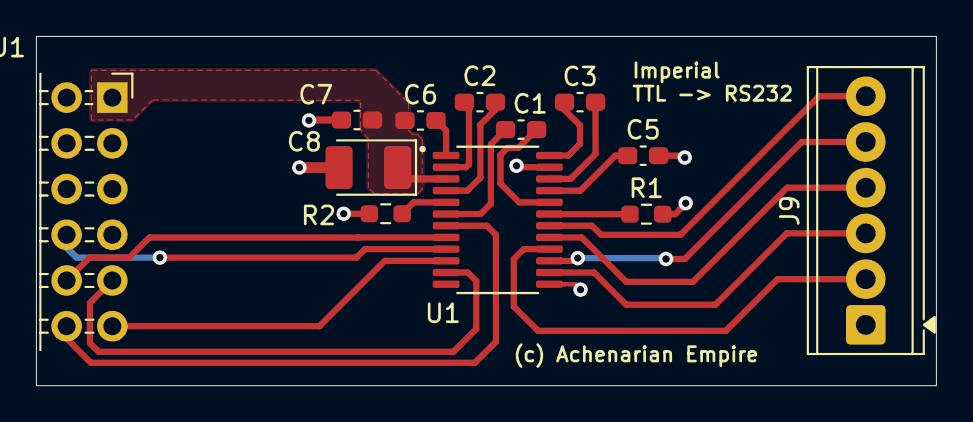
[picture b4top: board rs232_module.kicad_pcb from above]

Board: 2 copper layers, 50.0 x 19.4 mm, 12 parts (0 on the bottom side), 22 nets.

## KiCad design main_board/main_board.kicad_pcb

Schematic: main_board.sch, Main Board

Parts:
MK1, MK2, MK3, MK4: Mounting_Hole; MountingHole_2.2mm_M2_DIN965

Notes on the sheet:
USB Port and Power Generation
Top Level of USB Debugger project

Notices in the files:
parts and their libraries:
© Achenarian Empire
